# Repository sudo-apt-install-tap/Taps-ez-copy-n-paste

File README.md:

# Taps-ez-copy-n-paste

## Intro

This is a hackpad based project. It has 4 MX keys and 1 0.91" OLED With a RGB led. The micro controler used is a XIAO 2040. This will allow users to easily use macros like copy past and others.

## PCB Design And 3D View

<br>

<br>

<br>

## Full CAD Assembly

This Project Features a Open Design To Facilitate geeky behaviours!
<br>
P.S: THIS WAS TOTALLY 100% NOT BECAUSE I WAS TIRED OF CAD.<br>

<br><br>

## Build Images

<br>

Tape to hold the PCB in the case!
<br>

<br>

<br>

<br>

<br>

## Bill of Materials (BOM)

| Item     | Part Name                | Quantity |
|----------|---------------------------|----------|
| MCU      | XIAO RP2040               | 1        |
| Switches | MX Push Switches          | 4        |
| Display  | 0.91" OLED (128×32)       | 1        |
| Case     | 3D Printed Case           | 1        |
| PCB      | Custom PCB                | 1        |

# This has been fully built with the help of **HACKCLUB x AMD | BLUEPRINT**

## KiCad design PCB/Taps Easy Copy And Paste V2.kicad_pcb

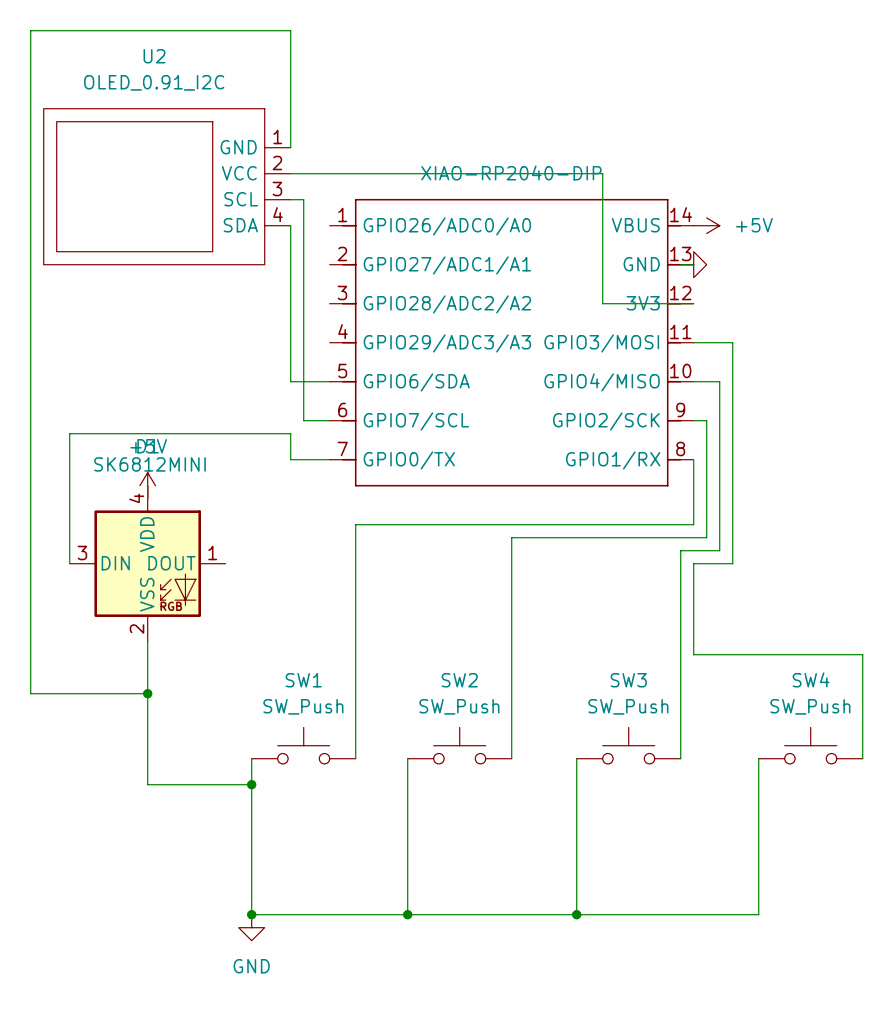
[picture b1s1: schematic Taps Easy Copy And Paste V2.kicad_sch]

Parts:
D1: SK6812MINI; LED_SK6812MINI_PLCC4_3.5x3.5mm_P1.75mm
SW1, SW2, SW3, SW4: SW_Push; SW_Cherry_MX_1.00u_PCB
U1: XIAO-RP2040-DIP
U2: OLED_0.91_I2C; PinHeader_1x04_P2.54mm_Vertical

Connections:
+5V: D1.4 (VDD), U1.14 (VBUS)
GND: D1.2 (VSS), SW1.1, SW2.1, SW3.1, SW4.1, U1.13 (GND), U2.1 (GND)
unnamed: D1.3 (DIN), U1.7 (GPIO0/TX)
unnamed: U1.12 (3V3), U2.2 (VCC)
unnamed: SW1.2, U1.8 (GPIO1/RX)
unnamed: SW2.2, U1.9 (GPIO2/SCK)
unnamed: SW4.2, U1.11 (GPIO3/MOSI)
unnamed: SW3.2, U1.10 (GPIO4/MISO)
unnamed: U1.5 (GPIO6/SDA), U2.4 (SDA)
unnamed: U1.6 (GPIO7/SCL), U2.3 (SCL)

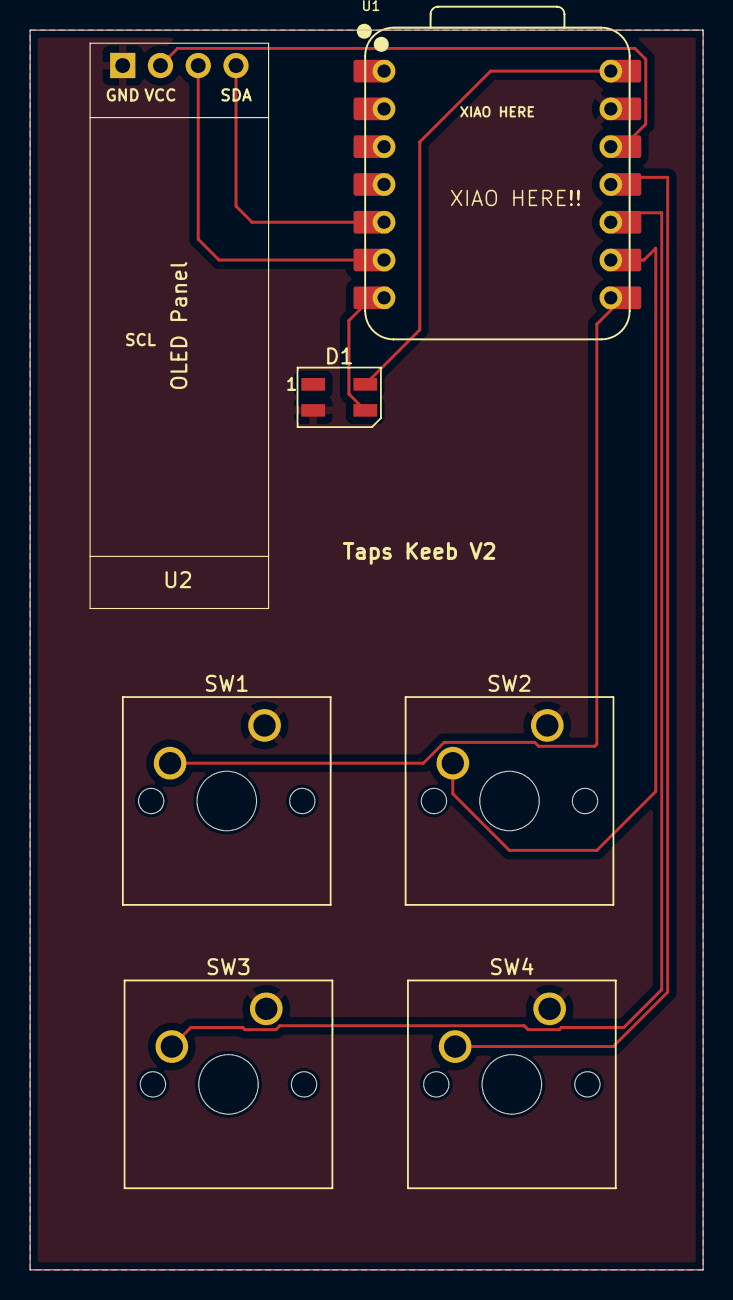
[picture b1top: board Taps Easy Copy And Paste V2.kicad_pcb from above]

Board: 2 copper layers, 45.2 x 83.3 mm, 7 parts (0 on the bottom side), 10 nets.

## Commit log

2025-12-06 Create CAD/
2025-12-06 Update f
2025-12-06 Create d
2025-12-06 Create s
2025-12-06 Create 1
2026-01-27 Refactor main.py for keyboard and display setup
2026-01-27 Add images to README for better visualization
    Added images to enhance project documentation.
2026-01-29 Added /Build Images
2026-01-29 Enhance README with CAD assembly and build images
    Added sections for CAD assembly and build images to README.
2026-01-29 Correct PCB in README section title
